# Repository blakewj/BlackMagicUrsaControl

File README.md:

# BlackMagicUrsaControl
BlackMagic Arduino Ursa Control (BMA)

Current ip: is 192.169.10.180

Installation :
-Install the BMA Near the camera

-Plug In SDI From SDI Out On The BMA(Which is the one nearest the centre)

-Power BMA Via The 9-12V dc port On the Black Magic Arduino Shield(Not The One Directly Attached to The Arduino Itself )

-Attach Network Cable (RJ45) to Ethernet Shield On The BMA
-Once Powered Continue On

Instructions:

-Type In (192.168.10.180) to your browser of choice, BMA has been tested with Chrome and safari.

-Once logged on You Should Now Have Control,

-when sending slider values you select your current Value Which is displayed Below The Slider then press the Button above the slider which will send the current command to the BMA

-When you have sent your first request a second webpage will pop up and will look identical to the previous,** note that the second page has a open connection to the BMA and will no open up any more pages when used to send commands,**this is due to a unresolved BUG**
 
Please Refer To Source Code For More In-depth details.

All commands must be structured in the following manner 
                         
192.168.10.180?COMMAND&
{Arduino shield}(start command){your command}(End of command)

End of command is &
Start of command is ?

Push buttons -

	Auto appeture —— ?APP&
	Auto focus — ?AF&

Slider value or relative valuables

Same command structure with and append value 

192.168.10.180?COMMAND&VAL%
{Arduino shield}(start command){your command}(End of command){val}(End of Value)

End of command is &
Start of command is ?

Slider values 

Exposure —— ?EXP&%
Value range integer 0-n

White balance —?MWB&%
Value range integer 3200-7600
icrement 100

F-stop —— ?FS&%
Value Range Floating Point -1.0 — -16.0
Sensor Gain ——- ?SG&%
Value range integer 1-16

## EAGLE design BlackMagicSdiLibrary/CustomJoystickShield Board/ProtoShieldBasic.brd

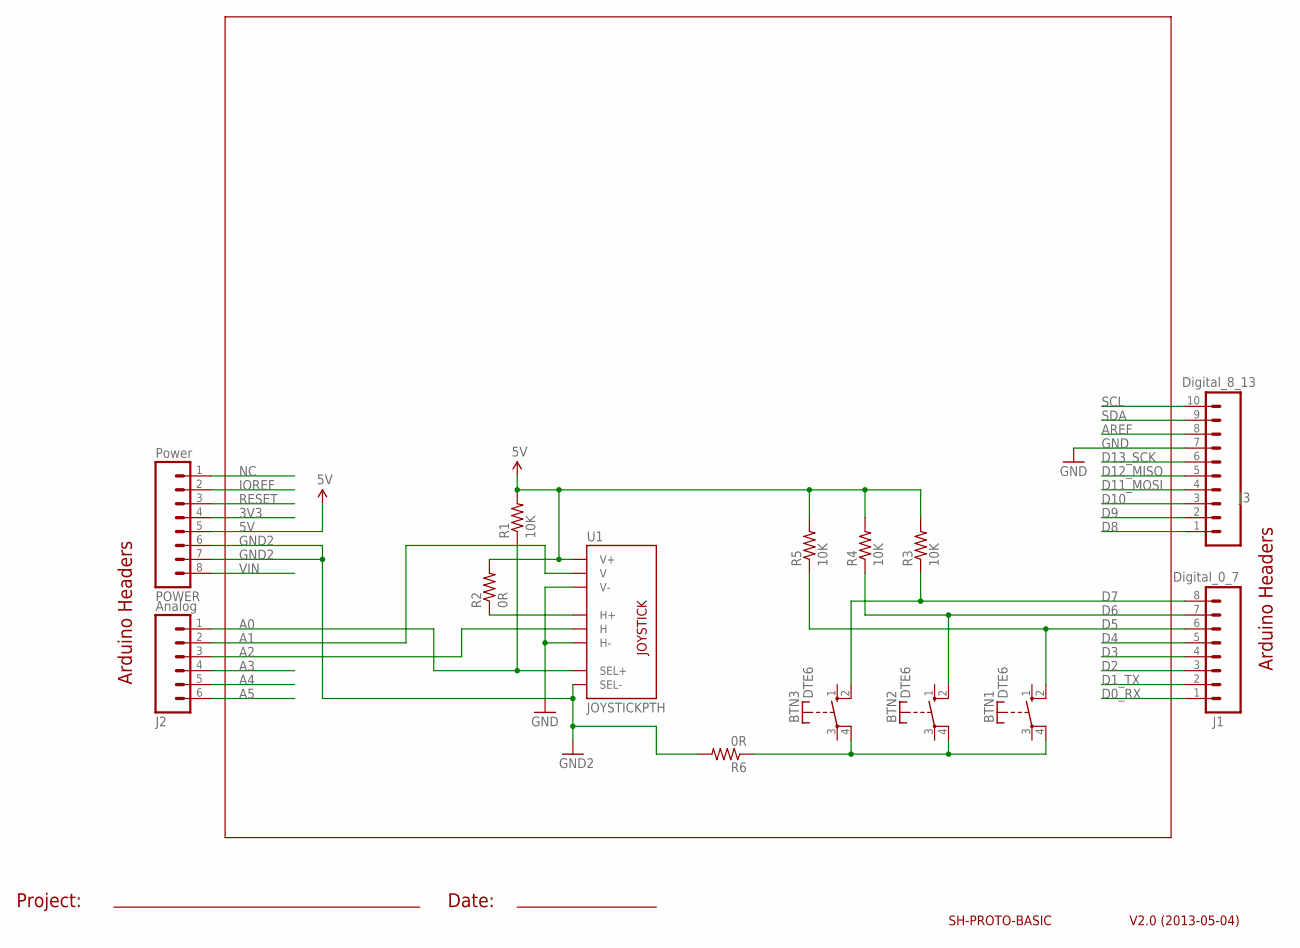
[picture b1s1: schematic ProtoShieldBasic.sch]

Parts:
BTN1, BTN2, BTN3: DTE6
J1: Digital_0_7; 1X08
J2: Analog; 1X06
J3: Digital_8_13; 1X10
POWER: Power; 1X08
R1, R3, R4, R5: 10K; 0207/10
R2, R6: 0R; 0207/10
U1: JOYSTICKPTH; JOYSTICK

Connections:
3V3: POWER.4
5V: POWER.5, R1.2, R2.2, R3.2, R4.2, R5.2, U1.V1 (V+)
A0: J2.1, R1.1, U1.B1A (SEL+)
A1: J2.2, U1.V2 (V)
A2: J2.3, U1.H2 (H)
A3: J2.4
A4: J2.5
A5: J2.6
AREF: J3.8
D0_RX: J1.1
D1_TX: J1.2
D2: J1.3
D3: J1.4
D4: J1.5
D5: BTN1.2 (S), J1.6, R5.1
D6: BTN2.2 (S), J1.7, R4.1
D7: BTN3.2 (S), J1.8, R3.1
D8: J3.1
D9: J3.2
D10: J3.3
D11_MOSI: J3.4
D12_MISO: J3.5
D13_SCK: J3.6
GND: J3.7, U1.H3 (H-), U1.V3 (V-)
GND2: POWER.6, POWER.7, R6.2, U1.B2A (SEL-)
IOREF: POWER.2
unnamed: R2.1, U1.H1 (H+)
NC: POWER.1
RESET: POWER.3
SCL: J3.10
SDA: J3.9
SW2: BTN1.4, BTN2.4, BTN3.4, R6.1
VIN: POWER.8

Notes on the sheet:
V2.0 (2013-05-04)
SH-PROTO-BASIC
Arduino Headers
Project:
Date:

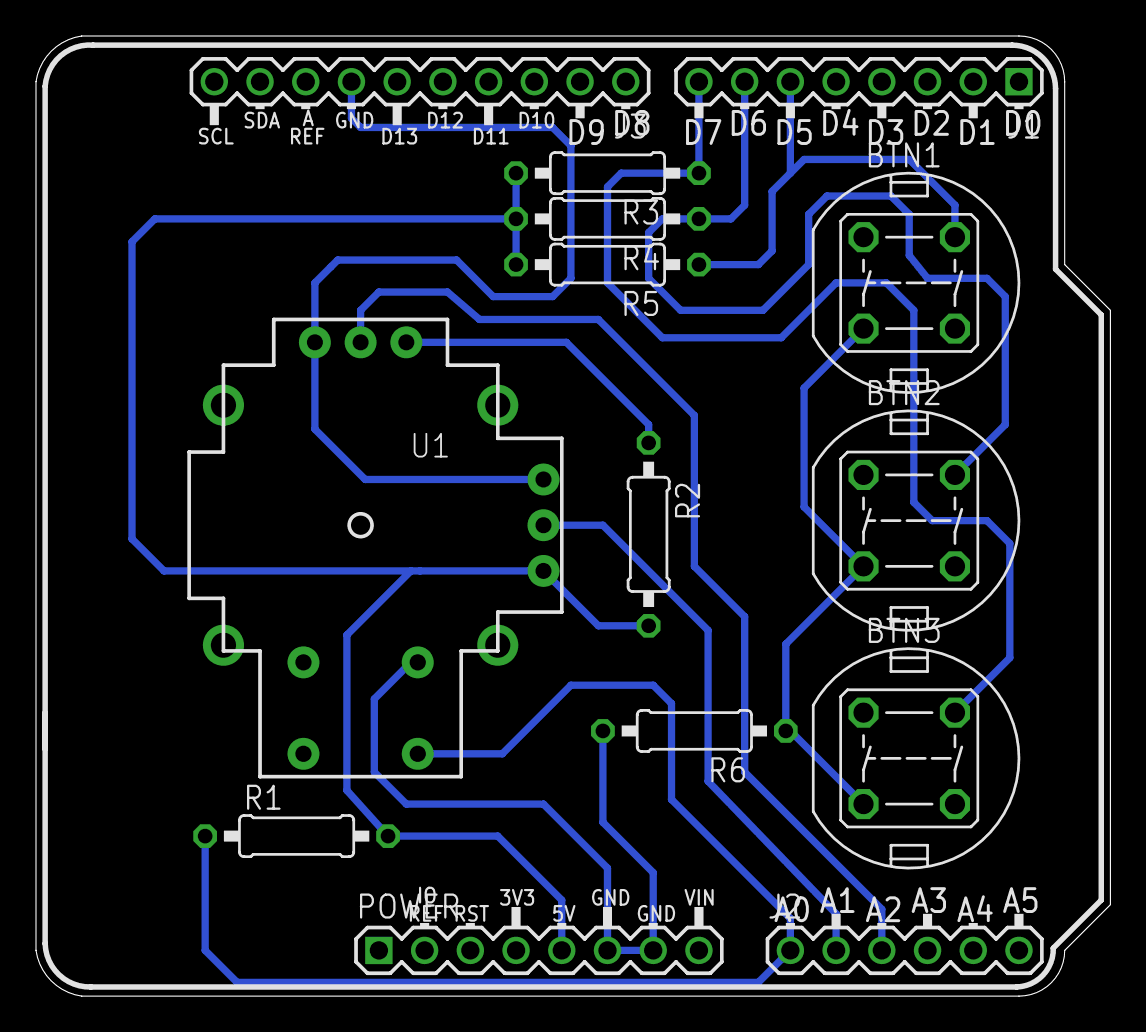
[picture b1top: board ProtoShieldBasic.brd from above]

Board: 2 copper layers, 59.7 x 53.3 mm, 14 parts (0 on the bottom side), 11 nets.

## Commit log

2017-08-02 Initial Commit
    working http function call
2017-08-02 Eclipse Project Commit
2017-08-02 removed old ino
2017-08-02 updated comments and funtion
    working funtion call
2017-08-02 update to slider function
    updated css for link buttons
2017-08-02 genreal patch
2017-08-02 patch
2017-08-02 Working final
    java script intergrated for Http Get to Send Slider Value
2017-08-02 Added Html Files To The Project
2017-08-03 Working Java Function
2017-08-03 added BlackMagic Test Functiond into Index.ino
2017-08-03 ammded HttP Structure
2017-08-03 post switch
    changed post to get
2017-08-03 tesing
2017-08-03 fixing the issue
2017-08-03 trouble shooting
2017-08-03 added blackmagic contol
2017-08-03 Fixed Http print issue
2017-08-03 Added Black Magic Library
2017-08-03 slider update
2017-08-03 added min.max to slider
2017-08-03 added step and default val
2017-08-03 fixed qoutes on slider
2017-08-03 slider update to post and range working
2017-08-03 updates names
2017-08-03 testing
2017-08-03 Ammeded range
2017-08-03 removed old html
2017-08-03 appeture added and all current controls seem to work
2017-08-03 genral tweaks
2017-08-03 added sensor gain
2017-08-03 almost there
2017-08-03 final push of the day
2017-08-04 updated the varibables and substing
2017-08-04 wokring substing
2017-08-04 new sliders
2017-08-04 update with all funtions
2017-08-04 added logo and edited css to look better
2017-08-04 Final Commit for working demo
2017-08-09 added some readme details
2017-08-10 Added More Notes
2017-08-10 white balance corrected
2017-08-26 im not sure

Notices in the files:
parts and their libraries:
SparkFun-Electromechanical: Licensing: Creative Commons ShareAlike 4.0 International - https://creativecommons.org/licenses/by-sa/4.0
